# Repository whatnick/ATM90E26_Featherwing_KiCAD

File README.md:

# ATM90E26_Featherwing_KiCAD
ATM90E26 Featherwing with ongoing development in KiCAD
- Previous Eagle version available here: https://github.com/whatnick/ATM90E26_Featherwing
- Arduino Library is available here: https://github.com/whatnick/ATM90E26_Arduino
- Micropython Library is available here: https://github.com/whatnick/ATM90E26_Micropython

# Connection to Host CPU
The boards can be connected in 2 ways with different corresponding jumper settings underneath the board:

- UART mode (default mode)

- SPI mode (requires resoldering of jumpers)
    - With CS on pin 9 
    - With CS on pin 10 

# Metering  modes
Using the MMD jumper various metering modes can be selected as specified by the datasheets.

# Connection to Voltage/Current samplers

The ATM90E26 can acquire 1 voltage and 2 current waveforms to perform energy measurement.
- Voltage sampling using step-down transformer (9V-12V) and voltage divider
- Current sampling using CT with multiplier resistor

# Licence Details
- Hardware License: TAPR 1.0
- Software License: MIT
- Documentation License: CC BY 4.0 International

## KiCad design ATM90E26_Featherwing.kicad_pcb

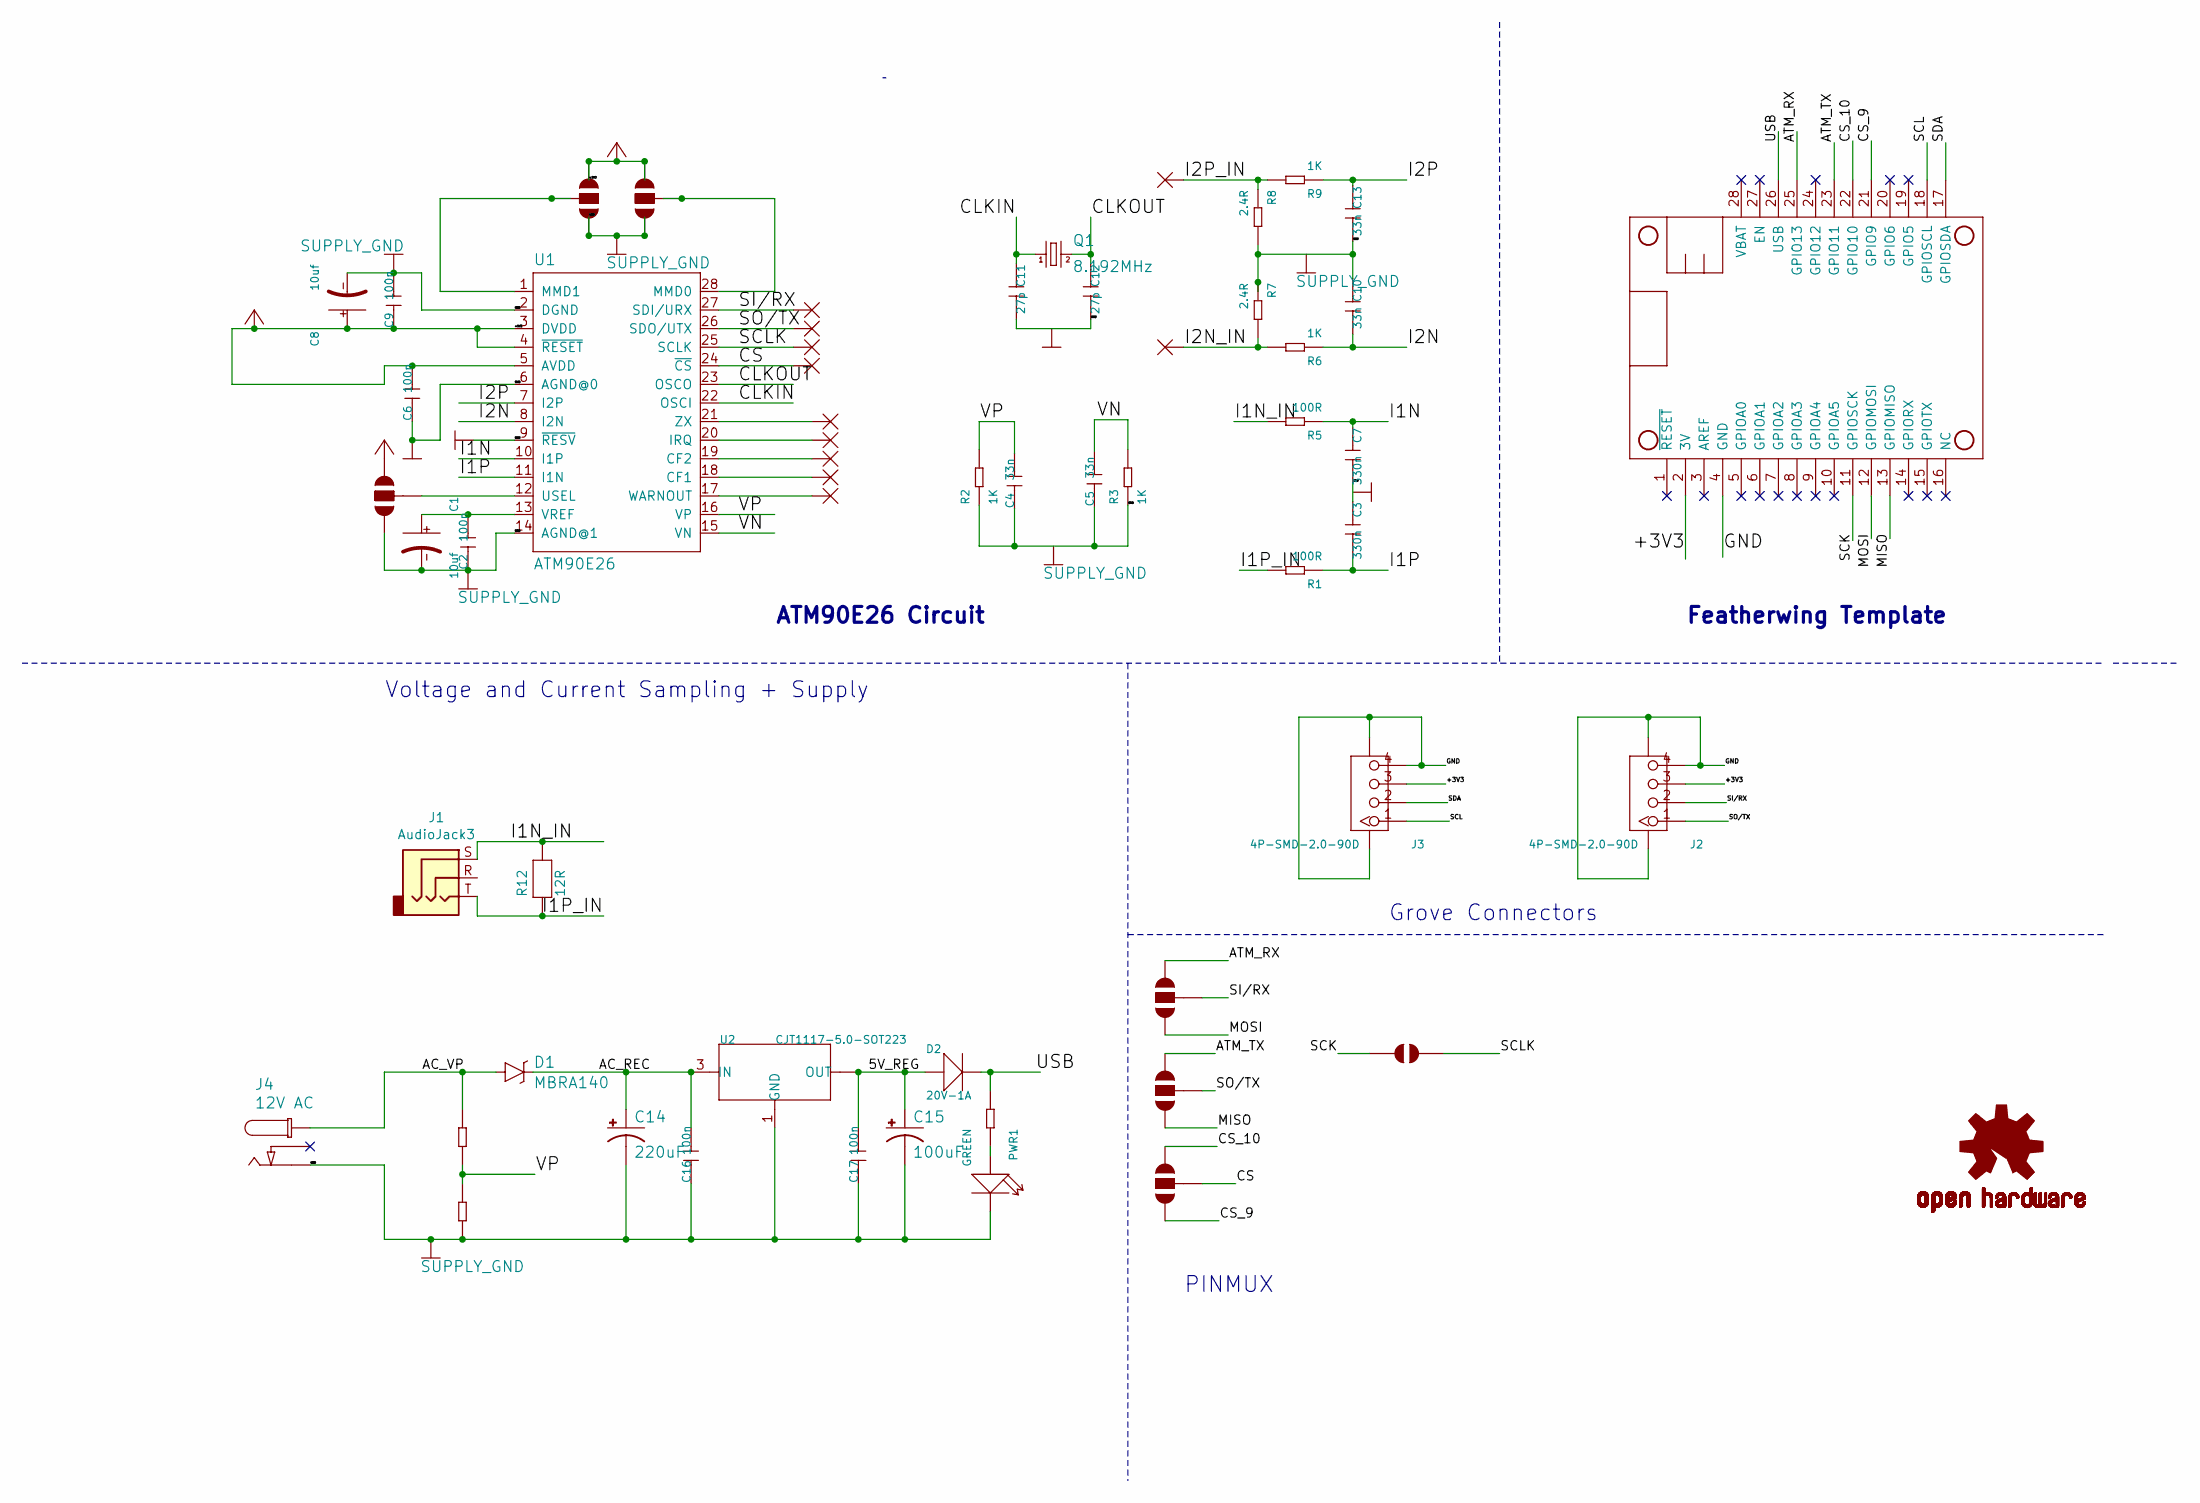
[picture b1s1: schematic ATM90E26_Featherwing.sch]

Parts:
C1, C8: 10uf; AVX-A
C2, C6, C9, C16, C17: 100n; C0603
C3, C7: 330n; C0603
C4, C5, C10, C13: 33n; C0603
C11, C12: 27p; C0603
C14: 220uF; 140CLH-1010
C15: 100uF; 153CLV-0605
CF1, CF2: WIREPADSMD1,27-254; SMD1,27-2,54
CS1: WIREPADSMD1,27-254; SMD1,27-2,54
CSMUX1: JUMPER-PAD-3-NOYES_SILK; PAD-JUMPER-3-NO_YES_SILK
D1: MBRA140; SMA-DIODE
D2: 20V-1A; SOD-123
I2N_IN1, I2P_IN1: WIREPADSMD1,27-254; SMD1,27-2,54
INT1: WIREPADSMD1,27-254; SMD1,27-2,54
J1: AudioJack3; Jack_3.5mm_CUI_SJ-3523-SMT_Horizontal
J2, J3: 4P-SMD-2.0-90D; HW4-SMD-2.0-90D
J4: 12V AC; DC_BARREL_JACK_SMD_2MM
LOGO1: OSHW-LOGOM; OSHW-Logo2_7.3x6mm_Copper
MMD0, MMD1: JUMPER-PAD-3-NOFULL_BOX_SILK; PAD-JUMPER-3-NO_YES_SILK_FULL_BOX
MS1: FEATHERWING_NODIM; FEATHERWING_DIM
PWR1: GREEN; LED-0603
Q1: 8.192MHz; HC49UP
R1, R5: 100R; R0603
R2, R3, R6, R9, R13: 1K; R0603
R7, R8: 2.4R; R0603
R10: 100K; R0603
R11: INF; R0603
R12: 12R; 0805
RXMUX1: JUMPER-PAD-3-NOYES_SILK; PAD-JUMPER-3-NO_YES_SILK
SCKMUX1: JUMPER-PAD-2-NOYES_SILK; PAD-JUMPER-2-NO_YES_SILK
SCLK1: WIREPADSMD1,27-254; SMD1,27-2,54
SI/RX1: WIREPADSMD1,27-254; SMD1,27-2,54
SO/TX1: WIREPADSMD1,27-254; SMD1,27-2,54
TXMUX1: JUMPER-PAD-3-NOYES_SILK; PAD-JUMPER-3-NO_YES_SILK
U1: ATM90E26; SSOP-28
U2: CJT1117-5.0-SOT223; SOT-223
USEL1: JUMPER-PAD-3-NOFULL_BOX_SILK; PAD-JUMPER-3-NO_YES_SILK_FULL_BOX
WARN1: WIREPADSMD1,27-254; SMD1,27-2,54
ZX1: WIREPADSMD1,27-254; SMD1,27-2,54

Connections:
+3V3: C6.2, C8.+, C9.1, J2.3, J3.3, MMD0.3, MMD1.1, MS1.2 (3V), U1.3 (DVDD), U1.4 (~RESET), U1.5 (AVDD), USEL1.3
/5V_REG: C15.+, C17.2, D2.+, U2.2 (OUT), U2.TER (OUT)
/AC_REC: C14.+, C16.2, D1.C, U2.3 (IN)
/AC_VP: D1.A, J4.P1@2 (P1), R10.1
/ATM_RX: MS1.25 (GPIO13), RXMUX1.3
/ATM_TX: MS1.23 (GPIO11), TXMUX1.3
/CLKIN: C11.1, Q1.1, U1.22 (OSCI)
/CLKOUT: C12.1, Q1.2, U1.23 (OSCO)
/CS: CS1.1, CSMUX1.2, U1.24 (~CS)
/CS_9: CSMUX1.1, MS1.21 (GPIO9)
/CS_10: CSMUX1.3, MS1.22 (GPIO10)
/I1N: C7.1, R5.1, U1.10 (I1P)
/I1N_IN: J1.S, R5.2, R12.2
/I1P: C3.2, R1.1, U1.11 (I1N)
/I1P_IN: J1.T, R1.2, R12.1
/I2N: C10.2, R6.1, U1.8 (I2N)
/I2N_IN: I2N_IN1.1, R6.2, R7.2
/I2P: C13.1, R9.1, U1.7 (I2P)
/I2P_IN: I2P_IN1.1, R8.1, R9.2
/MISO: MS1.13 (GPIOMISO), TXMUX1.1
/MOSI: MS1.12 (GPIOMOSI), RXMUX1.1
/SCK: MS1.11 (GPIOSCK), SCKMUX1.1
/SCL: J3.1, MS1.18 (GPIOSCL)
/SCLK: SCKMUX1.2, SCLK1.1, U1.25 (SCLK)
/SDA: J3.2, MS1.17 (GPIOSDA)
/SI/RX: J2.2, RXMUX1.2, SI/RX1.1, U1.27 (SDI/URX)
/SO/TX: J2.1, SO/TX1.1, TXMUX1.2, U1.26 (SDO/UTX)
/USB: D2.-, MS1.26 (USB), R13.1
/VN: C5.2, R3.2, U1.15 (VN)
/VP: C4.2, R2.2, R10.2, R11.1, U1.16 (VP)
GND: C1.-, C2.1, C3.1, C4.1, C5.1, C6.1, C7.2, C8.-, C9.2, C10.1, C11.2, C12.2, C13.2, C14.-, C15.-, C16.1, C17.1, J2.4, J2.SS1, J2.SS2, J3.4, J3.SS1, J3.SS2, J4.P2, MMD0.1, MMD1.3, MS1.4 (GND), PWR1.-, R2.1, R3.1, R7.1, R8.2, R11.2, U1.2 (DGND), U1.6 (AGND@0), U1.9 (~RESV), U1.14 (AGND@1), U2.1 (GND), USEL1.1
unnamed: C1.+, C2.2, U1.13 (VREF)
unnamed: CF1.1, U1.18 (CF1)
unnamed: CF2.1, U1.19 (CF2)
unnamed: INT1.1, U1.20 (IRQ)
unnamed: MMD0.2, U1.28 (MMD0)
unnamed: MMD1.2, U1.1 (MMD1)
unnamed: PWR1.+, R13.2
unnamed: U1.12 (USEL), USEL1.2
unnamed: U1.17 (WARNOUT), WARN1.1
unnamed: U1.21 (ZX), ZX1.1

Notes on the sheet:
ATM90E26 Circuit
Featherwing Template
Voltage and Current Sampling + Supply
Grove Connectors
PINMUX

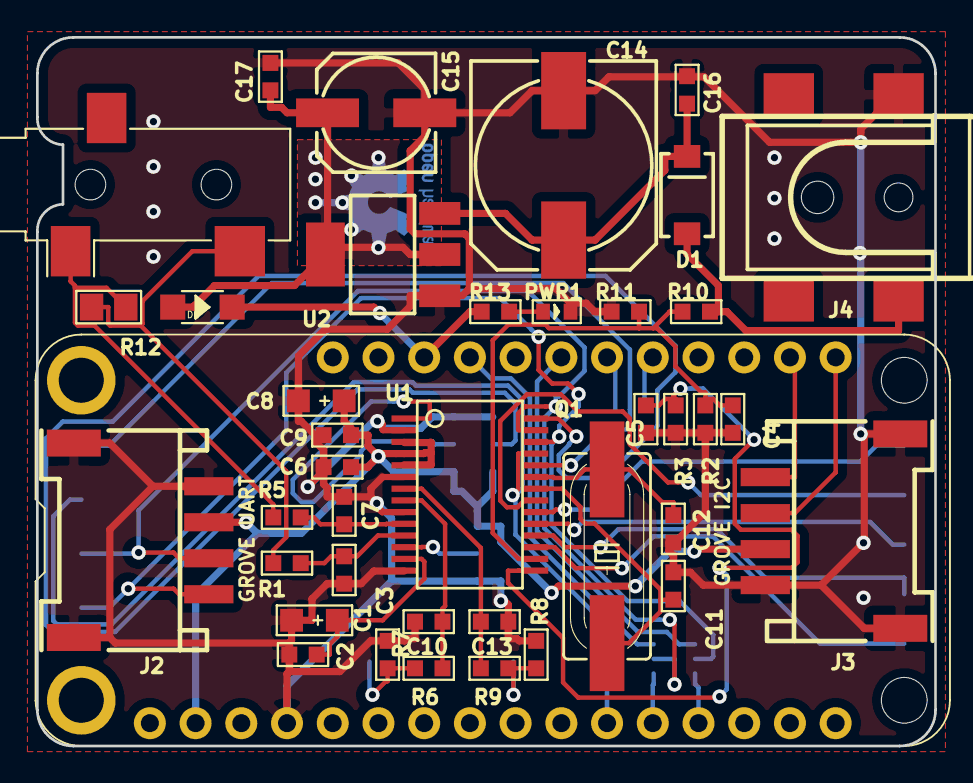
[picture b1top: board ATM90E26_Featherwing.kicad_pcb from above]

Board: 2 copper layers, 49.9 x 39.4 mm, 59 parts (0 on the bottom side), 41 nets.

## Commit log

2018-02-26 Initial kicad import
2018-02-26 Clean out tracks and zones, place parts
2018-02-27 Initial autoroute
2018-02-27 Complete route and clean up silk
2018-02-27 generate gerbers
2018-02-27 Ignore rar
2018-02-28 Adde some more 3d models
2018-04-21 Added jumpers documentation
2018-11-16 Fixed dangling/disconnected nodes
2018-11-18 Add no-connect to unused pins
2018-11-18 Connect R11 to ground
2018-11-18 pcb: connect R11 to ground
2018-11-20 ERC and connectivity (#1)
    * Add no-connect to unused pins
    * Connect R11 to ground
    * pcb: connect R11 to ground
2019-06-16 Converted to SJ-3525 for current clamp input
2019-06-16 Add stitchig vias
2019-12-22 New gerbers and git ignore of temp files
2019-12-22 Successfully fabricated and merged with 3-pin stereo (#2)
    * Converted to SJ-3525 for current clamp input
    * Add stitchig vias
    * New gerbers and git ignore of temp files
2019-12-22 Upgrade to KiCAD 5 and add iBOM
2019-12-22 Improved docs
2019-12-22 Added bullets on resource
2019-12-22 Add full iBOM
2020-01-04 Licence details as requested by OSHW certification
